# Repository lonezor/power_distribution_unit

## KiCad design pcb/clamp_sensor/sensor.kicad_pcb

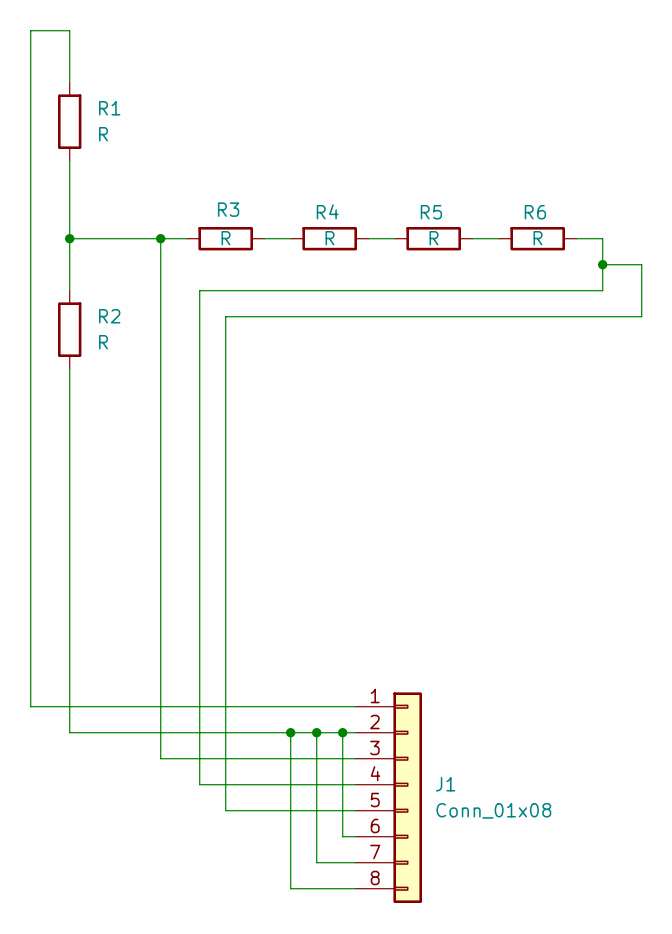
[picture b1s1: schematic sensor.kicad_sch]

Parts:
J1: Conn_01x08; PinHeader_1x08_P2.54mm_Vertical
R1, R2, R3, R4, R5, R6: R; R_Axial_DIN0207_L6.3mm_D2.5mm_P7.62mm_Horizontal

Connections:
unnamed: J1.1, R1.2
unnamed: J1.2, J1.6, J1.7, J1.8, R2.1
unnamed: J1.3, R1.1, R2.2, R3.2
unnamed: J1.4, J1.5, R6.1
unnamed: R3.1, R4.2
unnamed: R4.1, R5.2
unnamed: R5.1, R6.2

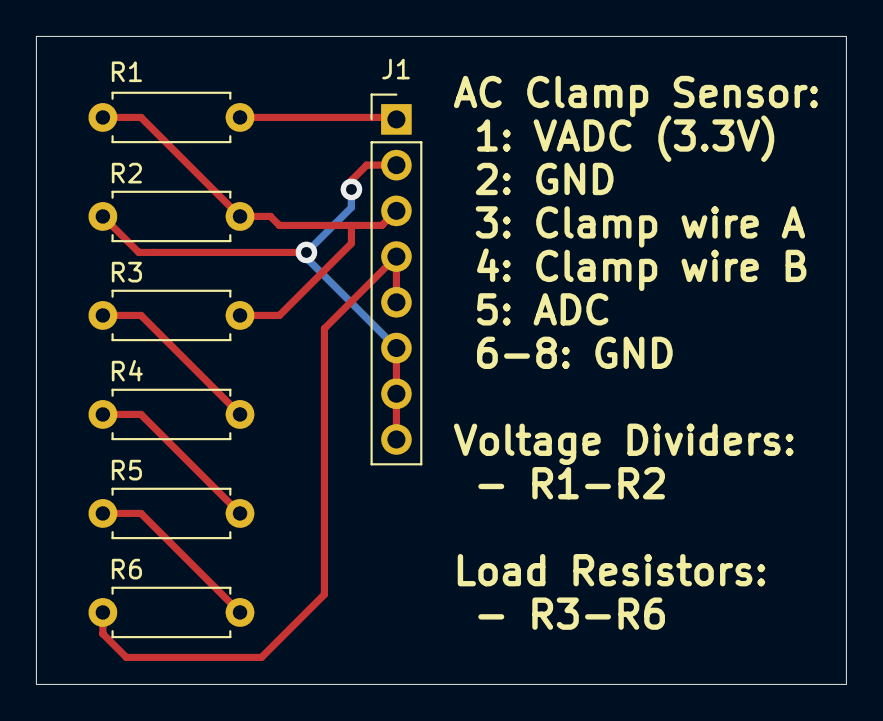
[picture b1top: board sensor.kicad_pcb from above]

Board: 2 copper layers, 45.0 x 36.0 mm, 7 parts (0 on the bottom side), 7 nets.

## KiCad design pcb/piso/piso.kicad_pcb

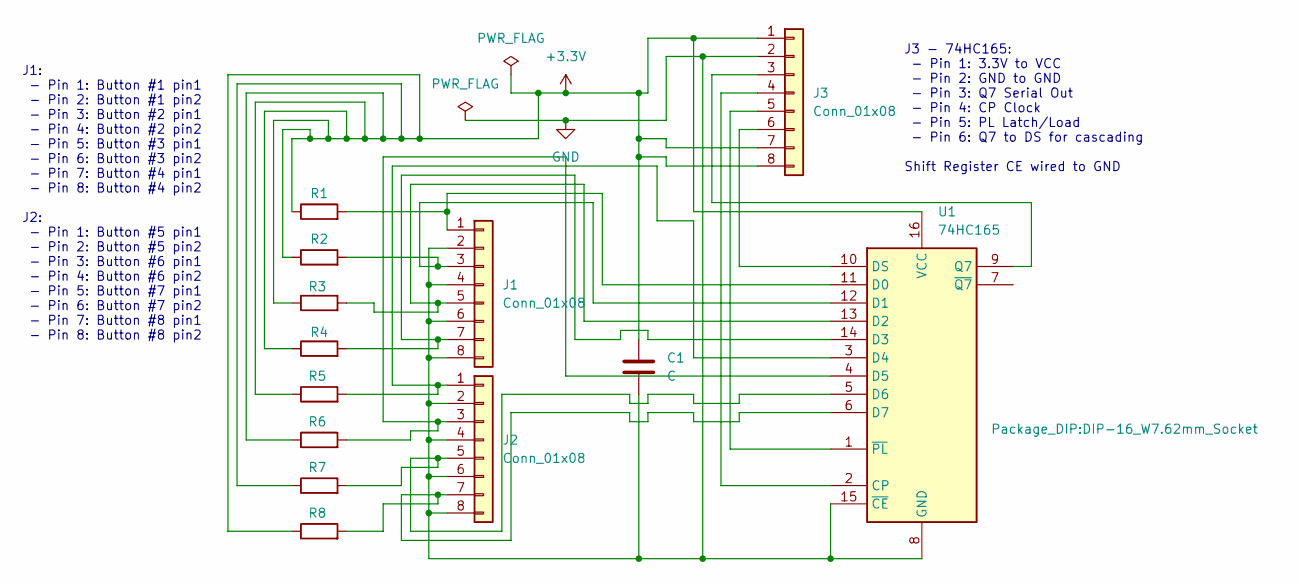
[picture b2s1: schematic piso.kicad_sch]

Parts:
C1: C; CP_Radial_Tantal_D5.5mm_P2.50mm
J1, J2, J3: Conn_01x08; PinHeader_1x08_P2.54mm_Vertical
R1, R2, R3, R4, R5, R6, R7, R8: R; R_Axial_DIN0207_L6.3mm_D2.5mm_P7.62mm_Horizontal
U1: 74HC165; DIP-16_W7.62mm_Socket

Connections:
+3.3V: C1.1, J3.1, J3.7, J3.8, R1.1, R2.1, R3.1, R4.1, R5.1, R6.1, R7.1, R8.1, U1.16 (VCC)
GND: C1.2, J1.2, J1.4, J1.6, J1.8, J2.2, J2.4, J2.6, J2.8, J3.2, U1.8 (GND), U1.15 (~CE)
unnamed: J1.1, R1.2, U1.11 (D0)
unnamed: J1.3, R2.2, U1.12 (D1)
unnamed: J1.5, R3.2, U1.13 (D2)
unnamed: J1.7, R4.2, U1.14 (D3)
unnamed: J2.1, R5.2, U1.3 (D4)
unnamed: J2.3, R6.2, U1.4 (D5)
unnamed: J2.5, R7.2, U1.5 (D6)
unnamed: J2.7, R8.2, U1.6 (D7)
unnamed: J3.3, U1.9 (Q7)
unnamed: J3.4, U1.2 (CP)
unnamed: J3.5, U1.1 (~PL)
unnamed: J3.6, U1.10 (DS)

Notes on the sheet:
J1: - Pin 1: Button #1 pin1 - Pin 2: Button #1 pin2 - Pin 3: Button #2 pin1 - Pin 4: Button #2 pin2 - Pin 5: Button #3 pin1 - Pin 6: Button #3 pin2 - Pin 7: Button #4 pin1 - Pin 8: Button #4 pin2 J2: - Pin 1: Button #5 pin1 - Pin 2: Button #5 pin2 - Pin 3: Button #6 pin1 - Pin 4: Button #6 pin2 - P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
J3 - 74HC165: - Pin 1: 3.3V to VCC - Pin 2: GND to GND - Pin 3: Q7 Serial Out - Pin 4: CP Clock - Pin 5: PL Latch/Load - Pin 6: Q7 to DS for cascading Shift Register CE wired to GND

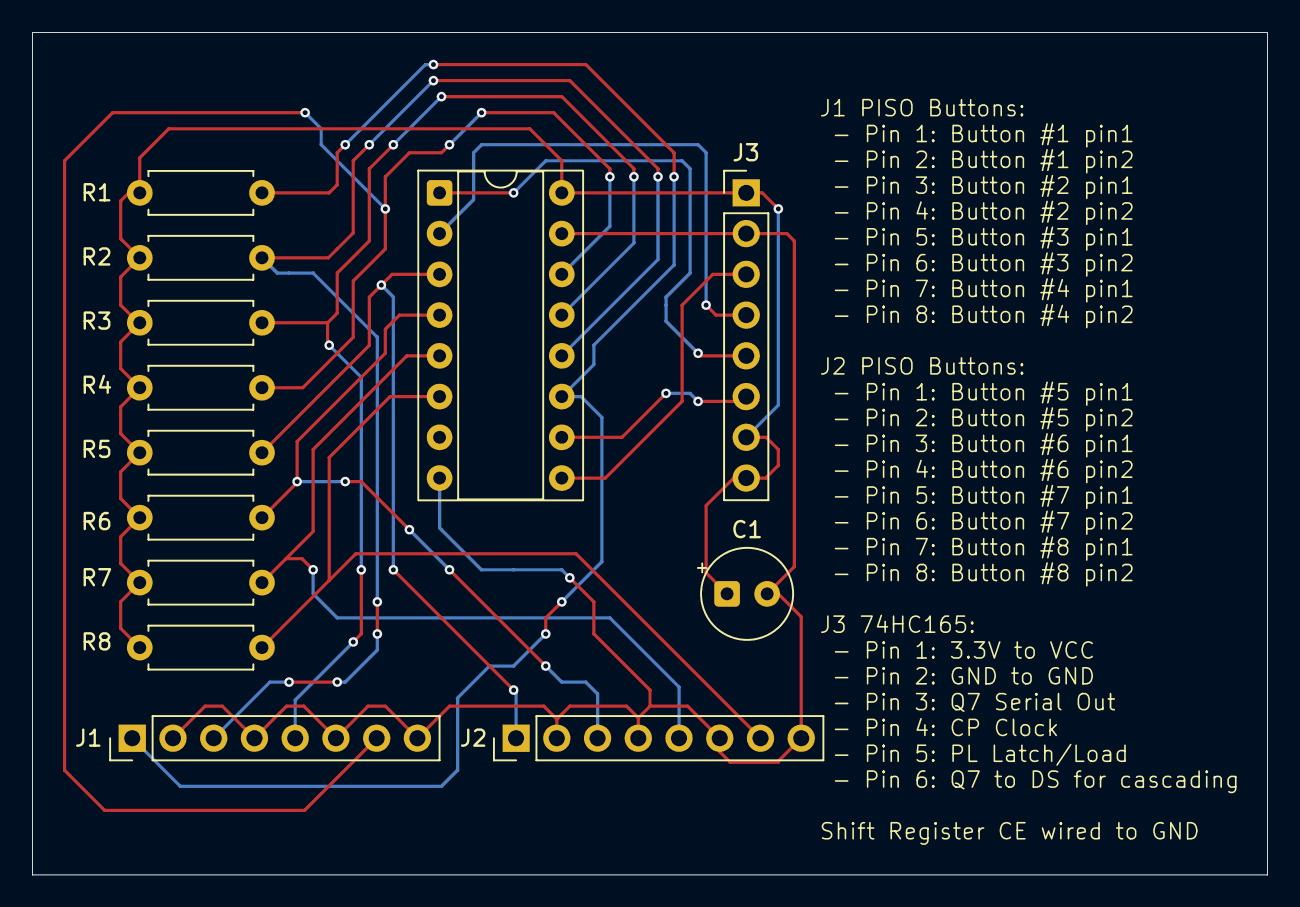
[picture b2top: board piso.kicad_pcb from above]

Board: 2 copper layers, 77.0 x 52.5 mm, 13 parts (0 on the bottom side), 14 nets.

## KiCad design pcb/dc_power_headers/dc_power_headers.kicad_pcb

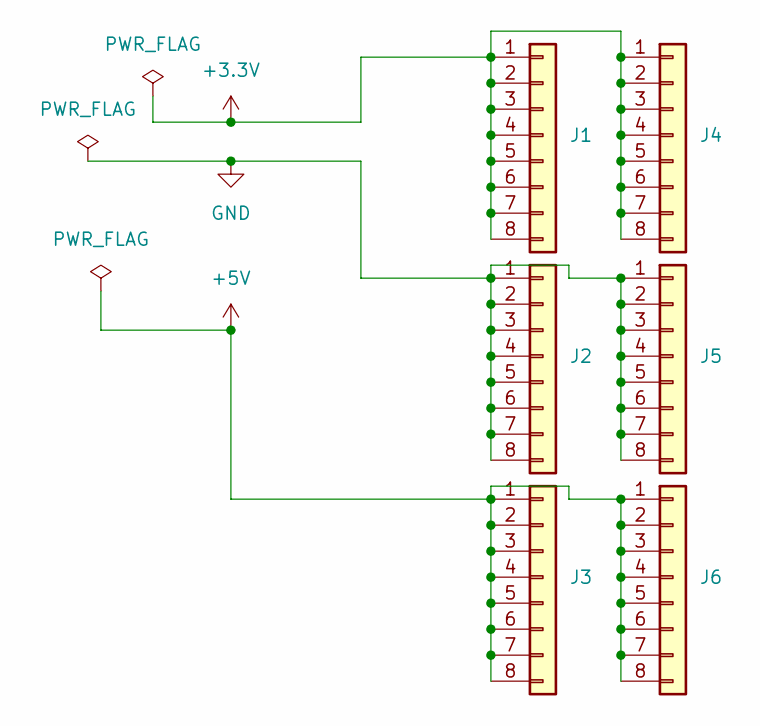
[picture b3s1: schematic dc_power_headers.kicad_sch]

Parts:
J1, J2, J3, J4, J5, J6: Conn_01x08; PinHeader_1x08_P2.54mm_Vertical

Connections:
+3.3V: J1.1, J1.2, J1.3, J1.4, J1.5, J1.6, J1.7, J1.8, J4.1, J4.2, J4.3, J4.4, J4.5, J4.6, J4.7, J4.8
+5V: J3.1, J3.2, J3.3, J3.4, J3.5, J3.6, J3.7, J3.8, J6.1, J6.2, J6.3, J6.4, J6.5, J6.6, J6.7, J6.8
GND: J2.1, J2.2, J2.3, J2.4, J2.5, J2.6, J2.7, J2.8, J5.1, J5.2, J5.3, J5.4, J5.5, J5.6, J5.7, J5.8

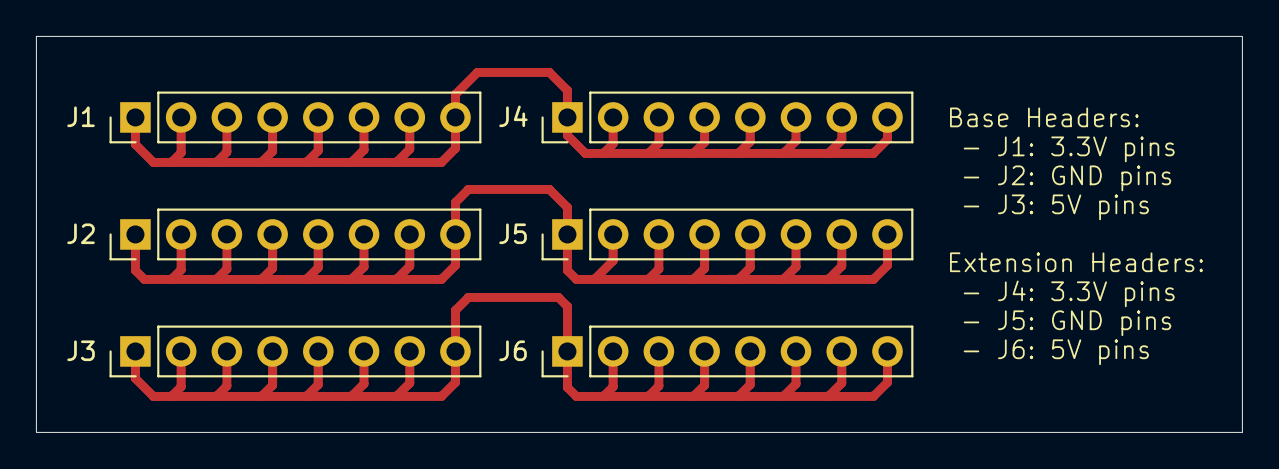
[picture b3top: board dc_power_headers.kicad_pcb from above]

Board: 2 copper layers, 67.0 x 22.0 mm, 6 parts (0 on the bottom side), 3 nets.

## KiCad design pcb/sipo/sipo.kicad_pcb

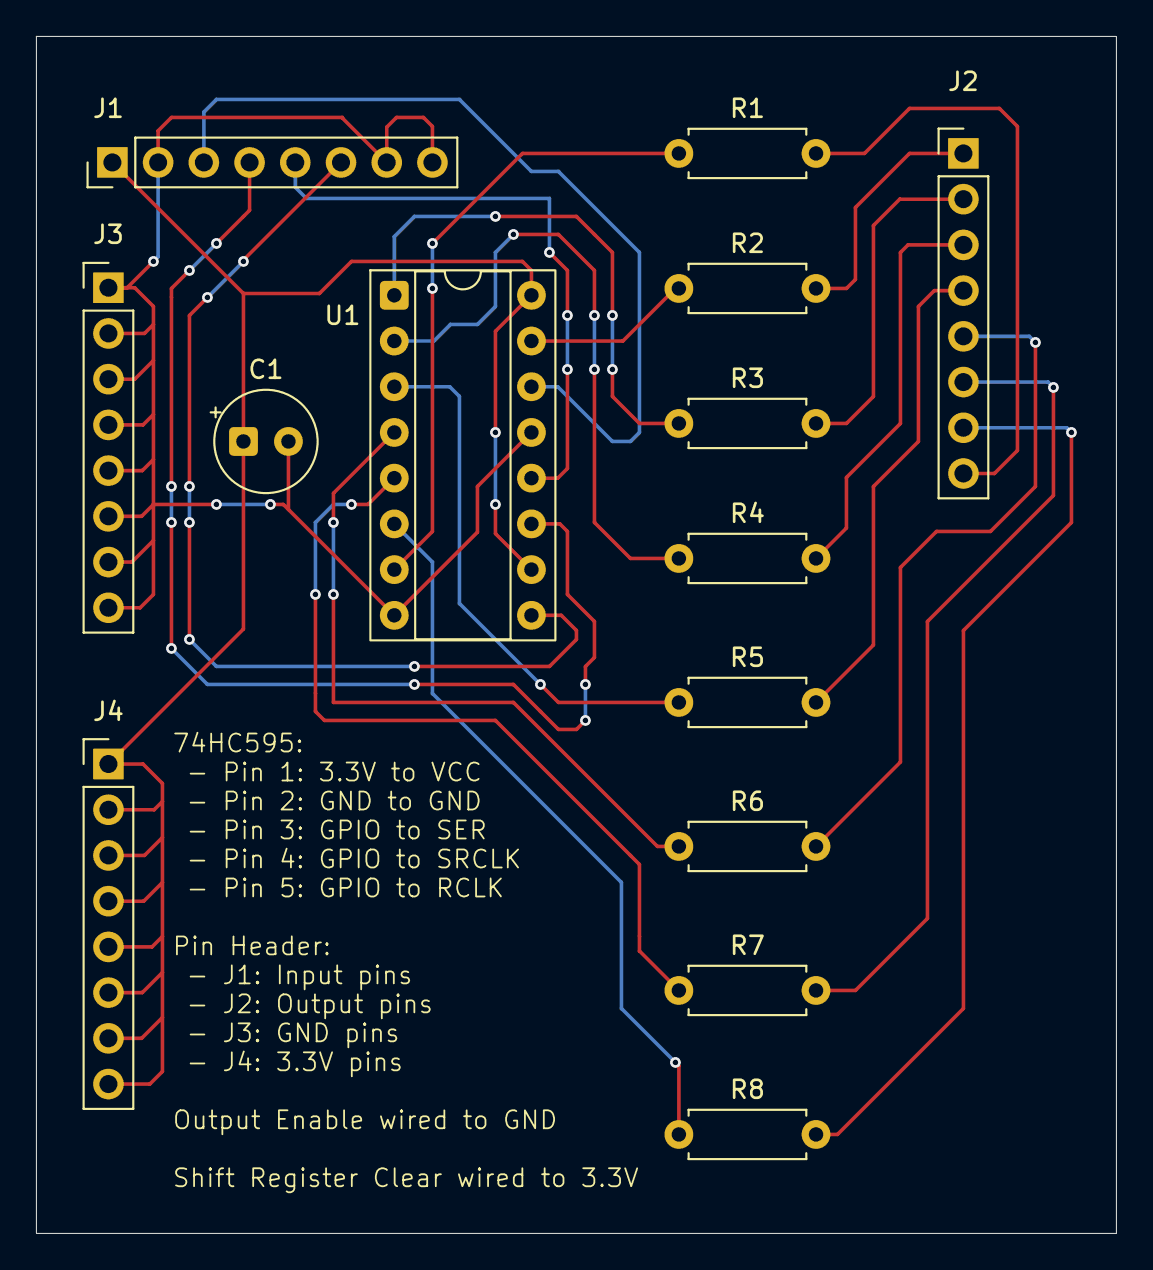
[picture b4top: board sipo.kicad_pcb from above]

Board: 2 copper layers, 60.0 x 66.5 mm, 14 parts (0 on the bottom side), 22 nets.

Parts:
C1: C; CP_Radial_Tantal_D5.5mm_P2.50mm
J1: Input pins; PinHeader_1x08_P2.54mm_Vertical
J2: Output pins; PinHeader_1x08_P2.54mm_Vertical
J3: GND pins; PinHeader_1x08_P2.54mm_Vertical
J4: 3.3V pins; PinHeader_1x08_P2.54mm_Vertical
R1, R2, R3, R4, R5, R6, R7, R8: R; R_Axial_DIN0207_L6.3mm_D2.5mm_P7.62mm_Horizontal
U1: 74HC595; DIP-16_W7.62mm_Socket

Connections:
+3.3V: C1.1, J1.1, J4.1, J4.2, J4.3, J4.4, J4.5, J4.6, J4.7, J4.8, U1.10 (~SRCLR), U1.16 (VCC)
GND: C1.2, J1.2, J1.7, J1.8, J3.1, J3.2, J3.3, J3.4, J3.5, J3.6, J3.7, J3.8, U1.8 (GND), U1.13 (~OE)
unnamed: J1.3, U1.14 (SER)
unnamed: J1.4, U1.11 (SRCLK)
unnamed: J1.5, U1.12 (RCLK)
unnamed: J1.6, U1.9 (QH')
unnamed: J2.1, R2.2
unnamed: J2.2, R3.2
unnamed: J2.3, R4.2
unnamed: J2.4, R5.2
unnamed: J2.5, R6.2
unnamed: J2.6, R7.2
unnamed: J2.7, R8.2
unnamed: J2.8, R1.2
unnamed: R2.1, U1.15 (QA)
unnamed: R3.1, U1.1 (QB)
unnamed: R4.1, U1.2 (QC)
unnamed: R5.1, U1.3 (QD)
unnamed: R6.1, U1.4 (QE)
unnamed: R7.1, U1.5 (QF)
unnamed: R8.1, U1.6 (QG)
unnamed: R1.1, U1.7 (QH)

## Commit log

2025-09-13 PCB: Add clamp sensor files
2025-09-13 Reference: Add RP2040_ETH_CODE.zip
2025-09-13 src: Add support for RP2040-ETH
    Board info:
    https://www.waveshare.com/wiki/RP2040-ETH
    The source code has been modified to match use case. Driver code switch from TCP to UDP.
    Configuration is not hard coded inside but via the API.
    Building/flashing using Arduino IDE 1.8.19. Note that custom board manager according to
    above URL is needed.
2025-09-14 Reference: Add Waveshare RP2040-ETH0 pin layout
2025-09-14 PCB: Add Serial-In / Parallel-out support (SIPO)
    This is based on the 74HC595 chip.
2025-09-14 PCB: Add DC power headers for 3.3V, GND and 5V
2025-09-14 RP2040-ETH: Define source code structure
    All projects rely on driver code via symlinks. Each module is
    given its own IP address.
2025-09-14 Raspberry_Pi: Add 32 channel relay code (I2C interface)
2025-09-28 Ethernet address update and live stats module
2025-09-28 Live stats now supports multiple data sources and zero padding
2025-09-29 Receiving messages over UDP now supported
2025-10-02 Stats interface is ready for use
2025-10-12 Functional relay stats simulator
2025-10-12 Add current sensor display test program
2025-10-12 Reduce brightness for displays in live stats module
2025-10-12 PCB: Add Parallel-In / Serial-out support (PISO)
    This is based on the 74HC165 chip.
2025-10-12 Documentation: Add front panel overview diagram
    Originally intended to be printed on the physical panel, but
    it requires too much space due to 3d printer limitations. It is good
    for README.md file however.
2025-10-12 First version of user interface A module
    Display 0 tested. More wiring needed to test the rest.
2025-10-12 Rename two directories
2025-10-15 Working setup for current sensor displays using two channel I2C setup
2025-10-18 Update live stats module to send states over UDP (25Hz)
2025-10-19 Align stat module behavior with first display feedback button
    This button controls both the first AC clamp display as well
    as the live stats module. They represents the control system
    overall and needs to have the same behavior.
    This makes it possible to completely turn off all non-essential
    LEDs
2025-11-02 User interface input #1: measure RMS samples analog input
2025-11-25 PCB: Clamp sensor update
